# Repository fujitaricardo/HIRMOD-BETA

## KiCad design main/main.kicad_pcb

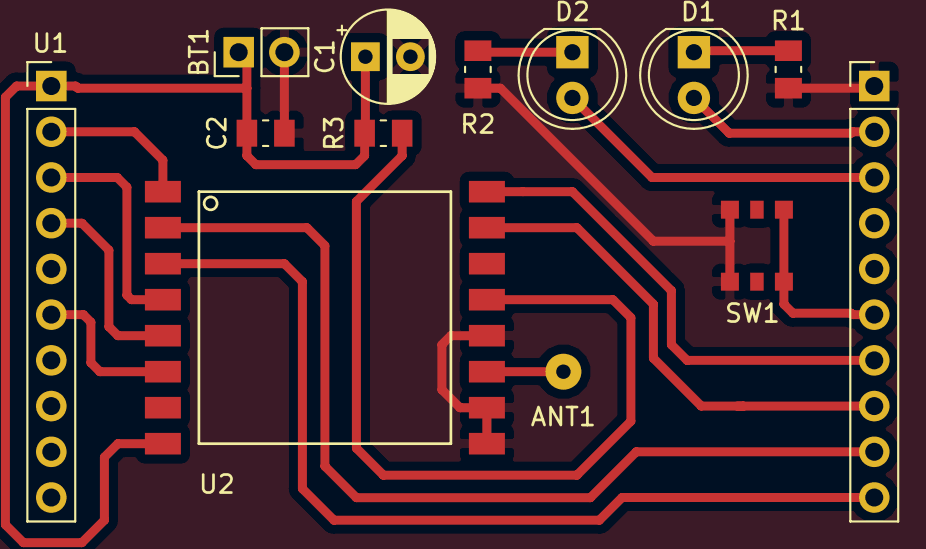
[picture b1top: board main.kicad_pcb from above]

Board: 2 copper layers, 12 parts (0 on the bottom side), 17 nets.

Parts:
ANT1: 433MHz_HELICOIDAL; SolderWirePad_single_0-8mmDrill
BT1: CR2477; PinHeader_1x02_P2.54mm_Vertical
C1: 10u; CP_Radial_D5.0mm_P2.50mm
C2: 100n; C_0805_2012Metric_Pad1.15x1.50mm_HandSolder
D1: RED; LED_D5.0mm
D2: IR; LED_D5.0mm
R1, R2: 1k; R_0805_2012Metric_Pad1.15x1.50mm_HandSolder
R3: 100k; R_0805_2012Metric_Pad1.15x1.50mm_HandSolder
SW1: CONFIG; SwitchButton_SMD_4x4mm
U1: MSP-EXP430FR2311_BoosterPack; BoosterPack_20pins
U2: RFM64W; RFM64W-433S2

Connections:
/IR: D2.2, U1.18
/IRQ_0: U1.14, U2.16
/IRQ_1: U1.13, U2.15
/MISO: U1.3, U2.4
/MOSI: U1.4, U2.5
/NSS_CFG: U1.12, U2.2
/NSS_DATA: U1.11, U2.3
/PB_CFG: SW1.1, U1.15
/POR: U1.2, U2.1
/RF_DATA: R3.2, U2.13
/SCLK: U1.6, U2.6
/STATUS: D1.2, U1.19
GND: BT1.2, C1.2, C2.2, R1.2, R2.2, SW1.2, U1.20, U2.9, U2.10, U2.12
unnamed: ANT1.1, U2.11
unnamed: D1.1, R1.1
unnamed: D2.1, R2.1
VDD: BT1.1, C1.1, C2.1, R3.1, U1.1, U2.8

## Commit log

2018-05-14 Added schematic, datasheets and linked library
2018-05-14 Replaced github libs for local ones and assigned footprints
2018-05-14 Added board layout
2018-05-14 Reduced board size
2018-05-14 Updated footprints in schematic
2018-05-17 Added MSP-EXP430FR2311 documentation
2018-05-17 Added new symbols and footprints
2018-05-17 Handmade version of RF BoosterPack for MSP-EXP430FR2311 board
2018-05-17 Updated BoosterPack board layout
2018-05-21 Updated Cap footprint to 5mm
2018-05-21 Replaced Cap Footprint to 5mm
